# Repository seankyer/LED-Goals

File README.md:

# LED-Goals: Goal-Setting Corkboard

LED-Goals is a personal project designed to help you track and visualize your long-term goals. It uses an LED strip to track the progress you make toward your goals over the course of a month.

I designed a custom PCB to connect the button, LED strip, and Arduino Nano together.

## YouTube
https://youtube.com/shorts/Iak79aCZ45Q?feature=share

## Hardware
- **PCB**: Custom-designed PCB to hold the necessary components.
- **LED Strip**: NeoPixel LED strip to visually represent your progress.
- **Button**: A button to increment progress and reset the LED strip when the goal is achieved.
- **Arduino Nano**: An Arduino Nano to control the LEDs and button logic.
- **9V Battery**: The system is powered by a 9V D-cell battery, making it portable.

## Software
The Arduino code controls the NeoPixel strip and button logic. It gradually fills the LED strip based on button presses or time, and resets when the goal is complete.

### Key Functions:
- **Incrementing LEDs**: Each press of the button adds one more LED to the strip.
- **Resetting LEDs**: When the strip is filled, pressing the button resets the strip back to 0 LEDs.

## Installation
1. **Hardware Setup**: Solder the components to the custom PCB, ensuring the button and LED strip are connected to the appropriate pins on the Arduino Nano.
2. **Software**: Download and install the Arduino IDE. Open the provided Arduino sketch, upload it to your Arduino Nano, and you're ready to start tracking your goals!

## Usage
Once powered on, the LEDs will gradually light up over the course of a month. Pressing the push-button will manually light up an addtional LED. When all LEDs are lit, pressing the button again will reset the strip.

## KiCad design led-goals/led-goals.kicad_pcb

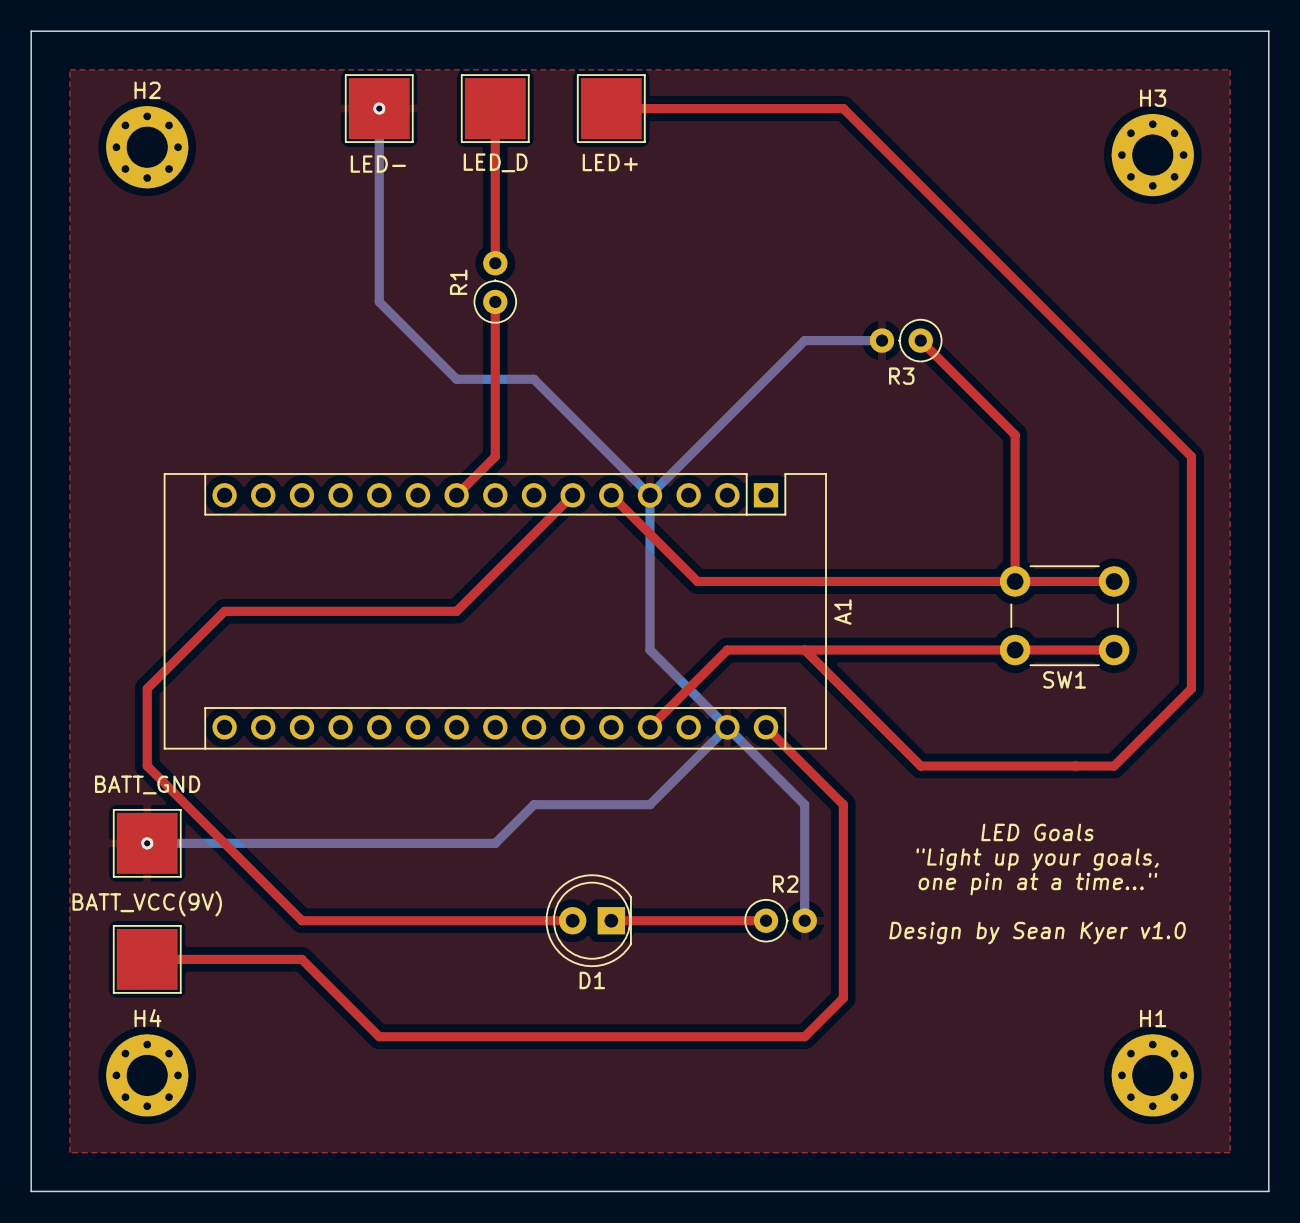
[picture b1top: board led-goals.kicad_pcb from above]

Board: 2 copper layers, 81.3 x 76.2 mm, 15 parts (0 on the bottom side), 8 nets.

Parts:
A1: Arduino_Nano_v3.x; Arduino_Nano
D1: LED; LED_D5.0mm
H1, H2, H3, H4: MountingHole; MountingHole_2.7mm_Pad_Via
J1: GND(9V); TestPoint_Pad_4.0x4.0mm
J2: VCC(9V); TestPoint_Pad_4.0x4.0mm
J3: LED+; TestPoint_Pad_4.0x4.0mm
J4: LED_D; TestPoint_Pad_4.0x4.0mm
J5: LED-; TestPoint_Pad_4.0x4.0mm
R1, R2, R3: R330; R_Axial_DIN0207_L6.3mm_D2.5mm_P2.54mm_Vertical
SW1: SW_Push; SW_PUSH_6mm_H7.3mm

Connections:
GND: A1.4 (GND), A1.29 (GND), J1.1 (GND), J5.1 (LEDSTRIP-), R2.2, R3.2
unnamed: A1.5 (D2), R3.1, SW1.2
unnamed: A1.6 (D3), D1.2 (A)
unnamed: A1.9 (D6), R1.1
unnamed: A1.27 (+5V), J3.1 (LED_Strip+), SW1.1
unnamed: A1.30 (VIN), J2.1 (VCC(9V))
unnamed: D1.1 (K), R2.1
unnamed: J4.1 (LEDSTRIPD), R1.2

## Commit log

2025-04-10 Adding arduino and PCB files
2025-04-10 Added PCB images and video
